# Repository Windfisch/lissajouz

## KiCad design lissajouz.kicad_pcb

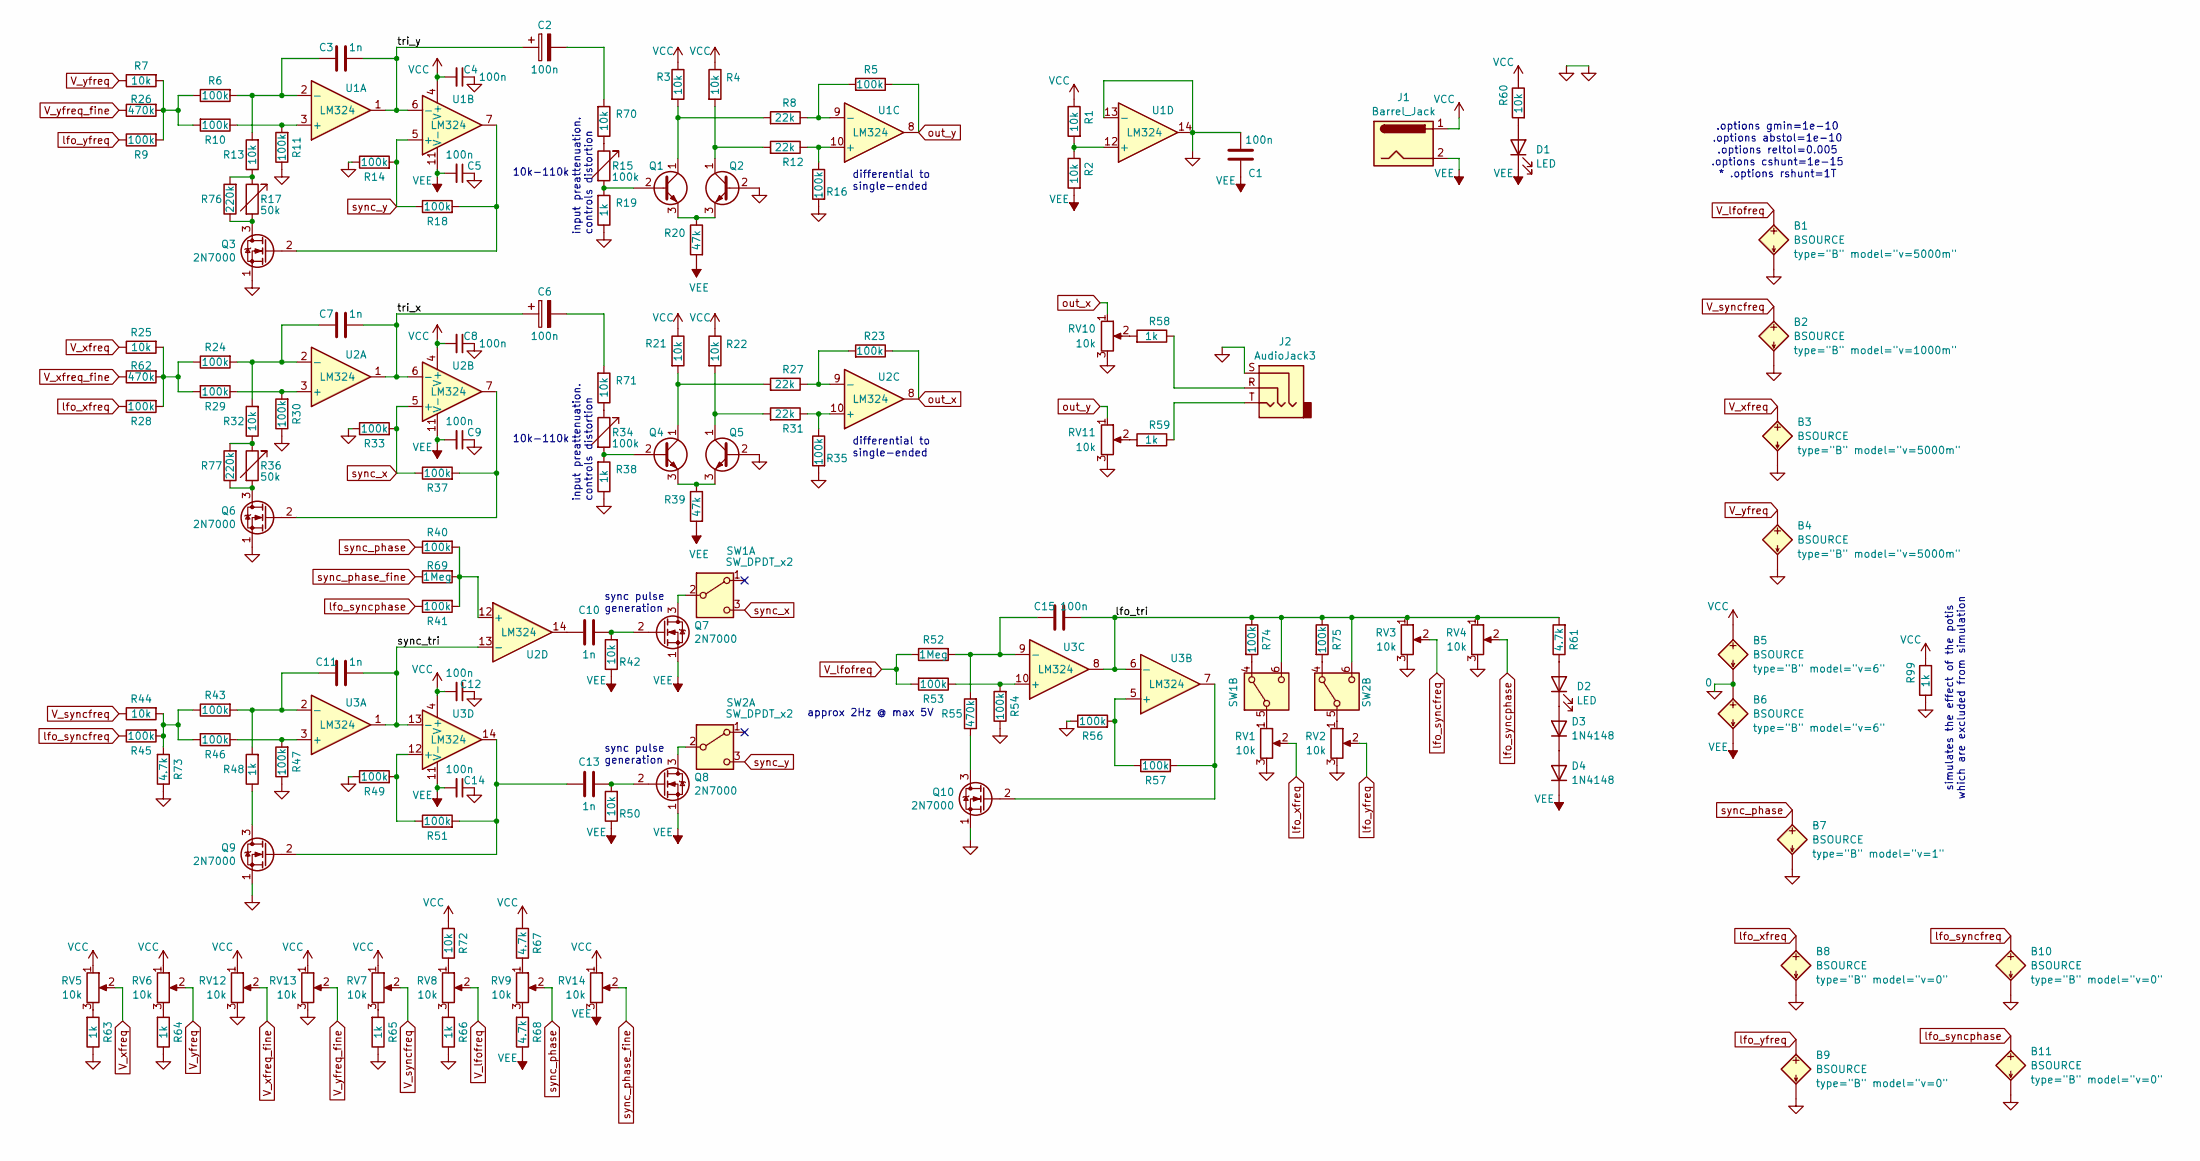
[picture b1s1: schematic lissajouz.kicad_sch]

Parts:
B1, B2, B3, B4, B5, B6, B7, B8, B9, B10, B11: BSOURCE
C1, C2, C4, C5, C6, C8, C9, C12, C14, C15: 100n; C_0805_2012Metric_Pad1.18x1.45mm_HandSolder
C3, C7, C10, C11, C13: 1n; C_0805_2012Metric_Pad1.18x1.45mm_HandSolder
D1, D2: LED; LED_D3.0mm
D3, D4: 1N4148; D_DO-35_SOD27_P7.62mm_Horizontal
J1: Barrel_Jack; myBarrelJack
J2: AudioJack3; Jack_3.5mm_CUI_SJ1-3535NG_Horizontal
Q1, Q2, Q4, Q5: BC547; TO-92_Inline
Q3, Q6, Q7, Q8, Q9, Q10: 2N7000; TO-92_Inline
R1, R2, R3, R4, R7, R13, R21, R22, R25, R32, R42, R44, R50, R60, R70, R71, R72: 10k; R_0805_2012Metric_Pad1.20x1.40mm_HandSolder
R5, R6, R9, R10, R11, R14, R16, R18, R23, R24, R28, R29, R30, R33, R35, R37, R40, R41, R43, R45, R46, R47, R49, R51, R53, R54, R56, R57, R74, R75: 100k; R_0805_2012Metric_Pad1.20x1.40mm_HandSolder
R8, R12, R27, R31: 22k; R_0805_2012Metric_Pad1.20x1.40mm_HandSolder
R15, R34: 100k; my_poti_Potentiometer_Alpha_RD901F-40-00D_Single_Vertical
R17, R36: 50k; my_poti_Potentiometer_Alpha_RD901F-40-00D_Single_Vertical
R19, R38, R48, R58, R59, R63, R64, R65, R66: 1k; R_0805_2012Metric_Pad1.20x1.40mm_HandSolder
R20, R39: 47k; R_0805_2012Metric_Pad1.20x1.40mm_HandSolder
R26, R55, R62: 470k; R_0805_2012Metric_Pad1.20x1.40mm_HandSolder
R52, R69: 1Meg; R_0805_2012Metric_Pad1.20x1.40mm_HandSolder
R61, R67, R68, R73: 4.7k; R_0805_2012Metric_Pad1.20x1.40mm_HandSolder
R76, R77: 220k; R_0805_2012Metric_Pad1.20x1.40mm_HandSolder
R99: 1k; R_0805_2012Metric_Pad1.15x1.40mm_HandSolder
RV1, RV2, RV3, RV4, RV5, RV6, RV7, RV8, RV9, RV12, RV13, RV14: 10k; my_poti_Potentiometer_Alpha_RD901F-40-00D_Single_Vertical
RV10, RV11: 10k; Potentiometer_Runtron_RM-065_Vertical
SW1, SW2: SW_DPDT_x2; switch8x8
U1, U2, U3: LM324; DIP-14_W7.62mm

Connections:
/lfo_tri: C15.1, R61.2, R74.1, R75.1, RV3.1, RV4.1, SW1.6 (C), SW2.6 (C), U3.6 (-), U3.8
/sync_tri: C11.1, U2.13 (-), U3.1, U3.13 (-)
/tri_x: C6.1, C7.1, U2.1, U2.6 (-)
/tri_y: C2.1, C3.1, U1.1, U1.6 (-)
GND: B1.2 (N-), B2.2 (N-), B3.2 (N-), B4.2 (N-), B7.2 (N-), B8.2 (N-), B9.2 (N-), B10.2 (N-), B11.2 (N-), C1.1, C4.1, C5.1, C8.1, C9.1, C12.1, C14.1, J2.S, Q2.2 (B), Q3.1 (S), Q5.2 (B), Q6.1 (S), Q9.1 (S), Q10.1 (S), R11.1, R14.1, R16.2, R19.1, R30.1, R33.1, R35.2, R38.1, R47.1, R49.1, R54.1, R56.1, R63.1, R64.1, R65.1, R66.1, R73.1, R99.2, RV1.3, RV2.3, RV3.3, RV4.3, RV10.3, RV11.3, RV12.3, RV13.3, U1.13 (-), U1.14
unnamed: B5.2 (N-), B6.1 (N+)
unnamed: C2.2, R70.2
unnamed: C6.2, R71.2
unnamed: C10.2, U2.14
unnamed: D1.2 (A), R60.2
unnamed: D2.2 (A), R61.1
unnamed: D2.1 (K), D3.2 (A)
unnamed: D3.1 (K), D4.2 (A)
unnamed: J2.R, R58.1
unnamed: J2.T, R59.1
unnamed: Q1.2 (B), R15.2, R19.2
unnamed: Q1.1 (C), R3.2, R8.2
unnamed: Q1.3 (E), Q2.3 (E), R20.1
unnamed: Q2.1 (C), R4.2, R12.2
unnamed: Q3.3 (D), R17.2, R76.1
unnamed: Q3.2 (G), R18.2, U1.7
unnamed: Q4.2 (B), R34.2, R38.2
unnamed: Q4.1 (C), R21.2, R27.2
unnamed: Q4.3 (E), Q5.3 (E), R39.1
unnamed: Q5.1 (C), R22.2, R31.2
unnamed: Q6.3 (D), R36.2, R77.1
unnamed: Q6.2 (G), R37.2, U2.7
unnamed: Q7.3 (D), SW1.2 (B)
unnamed: C10.1, Q7.2 (G), R42.2
unnamed: Q8.3 (D), SW2.2 (B)
unnamed: C13.1, Q8.2 (G), R50.2
unnamed: Q9.3 (D), R48.1
unnamed: C13.2, Q9.2 (G), R51.2, U3.14
unnamed: Q10.3 (D), R55.1
unnamed: Q10.2 (G), R57.2, U3.7
unnamed: R6.1, R7.2, R9.2, R10.2, R26.2
unnamed: R13.1, R17.1, R76.2
unnamed: R15.1, R70.1
unnamed: R24.1, R25.2, R28.2, R29.2, R62.2
unnamed: R32.1, R36.1, R77.2
unnamed: R34.1, R71.1
unnamed: R43.1, R44.2, R45.2, R46.2, R73.2
unnamed: R58.2, RV10.2
unnamed: R59.2, RV11.2
unnamed: R63.2, RV5.3
unnamed: R64.2, RV6.3
unnamed: R65.2, RV7.3
unnamed: R66.2, RV8.3
unnamed: R67.1, RV9.1
unnamed: R68.2, RV9.3
unnamed: R72.1, RV8.1
unnamed: R74.2, SW1.4 (A)
unnamed: RV1.1, SW1.5 (B)
unnamed: R75.2, SW2.4 (A)
unnamed: RV2.1, SW2.5 (B)
unnamed: R10.1, R11.2, U1.3 (+)
unnamed: C3.2, R6.2, R13.2, U1.2 (-)
unnamed: R12.1, R16.1, U1.10 (+)
unnamed: R5.2, R8.1, U1.9 (-)
unnamed: R1.2, R2.1, U1.12 (+)
unnamed: R29.1, R30.2, U2.3 (+)
unnamed: C7.2, R24.2, R32.2, U2.2 (-)
unnamed: R31.1, R35.1, U2.10 (+)
unnamed: R23.2, R27.1, U2.9 (-)
unnamed: R40.2, R41.2, R69.2, U2.12 (+)
unnamed: R46.1, R47.2, U3.3 (+)
unnamed: C11.2, R43.2, R48.2, U3.2 (-)
unnamed: R56.2, R57.1, U3.5 (+)
unnamed: R53.1, R54.2, U3.10 (+)
unnamed: C15.2, R52.2, R55.2, U3.9 (-)
unnamed: R49.2, R51.1, U3.12 (+)
VCC: B5.1 (N+), C4.2, C8.2, C12.2, J1.1, R1.1, R3.1, R4.1, R21.1, R22.1, R60.1, R67.2, R72.2, R99.1, RV5.1, RV6.1, RV7.1, RV12.1, RV13.1, RV14.1, U1.4 (V+), U2.4 (V+), U3.4 (V+)
VEE: B6.2 (N-), C1.2, C5.2, C9.2, C14.2, D1.1 (K), D4.1 (K), J1.2, Q7.1 (S), Q8.1 (S), R2.2, R20.2, R39.2, R42.1, R50.1, R68.1, RV14.3, U1.11 (V-), U2.11 (V-), U3.11 (V-)
V_lfofreq: B1.1 (N+), R52.1, R53.2, RV8.2
V_syncfreq: B2.1 (N+), R44.1, RV7.2
V_xfreq: B3.1 (N+), R25.1, RV5.2
V_xfreq_fine: R62.1, RV12.2
V_yfreq: B4.1 (N+), R7.1, RV6.2
V_yfreq_fine: R26.1, RV13.2
lfo_syncfreq: B10.1 (N+), R45.1, RV3.2
lfo_syncphase: B11.1 (N+), R41.1, RV4.2
lfo_xfreq: B8.1 (N+), R28.1, RV1.2
lfo_yfreq: B9.1 (N+), R9.1, RV2.2
out_x: R23.1, RV10.1, U2.8
out_y: R5.1, RV11.1, U1.8
sync_phase: B7.1 (N+), R40.1, RV9.2
sync_phase_fine: R69.1, RV14.2
sync_x: R33.2, R37.1, SW1.3 (C), U2.5 (+)
sync_y: R14.2, R18.1, SW2.3 (C), U1.5 (+)

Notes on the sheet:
differential to single-ended
sync pulse generation
simulates the effect of the potis which are excluded from simulation
approx 2Hz @ max 5V
10k-110k
input preattenuation. controls distortion
.options gmin=1e-10 .options abstol=1e-10 .options reltol=0.005 .options cshunt=1e-15 * .options rshunt=1T

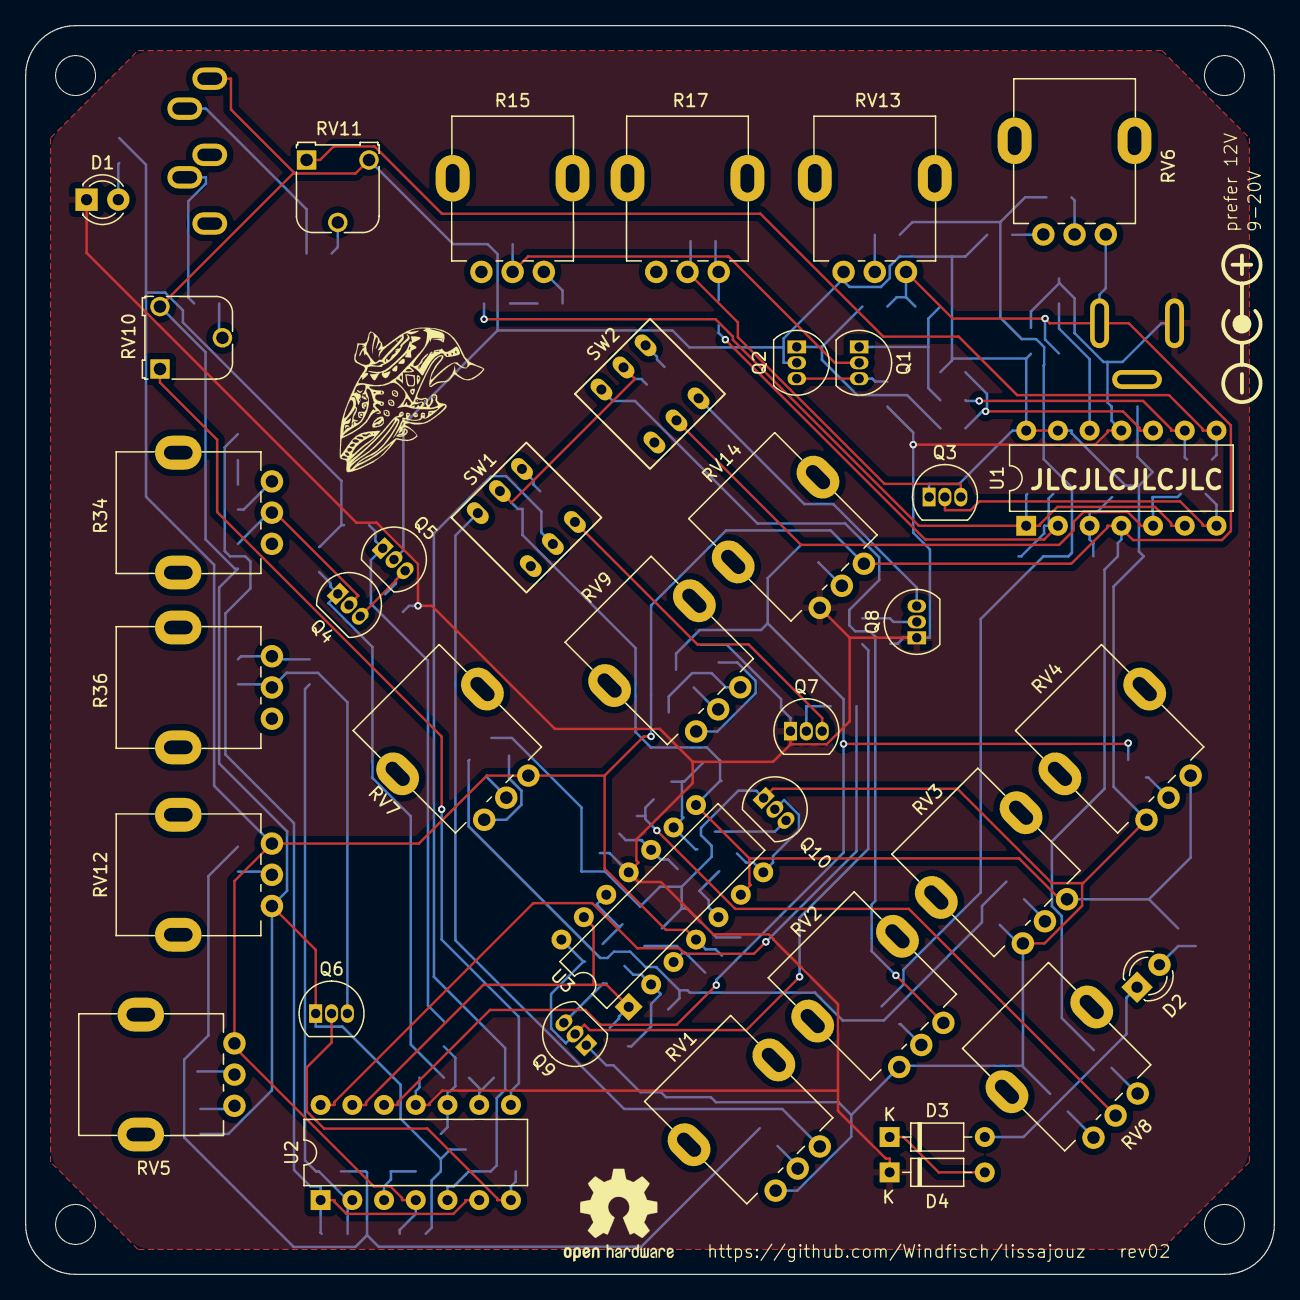
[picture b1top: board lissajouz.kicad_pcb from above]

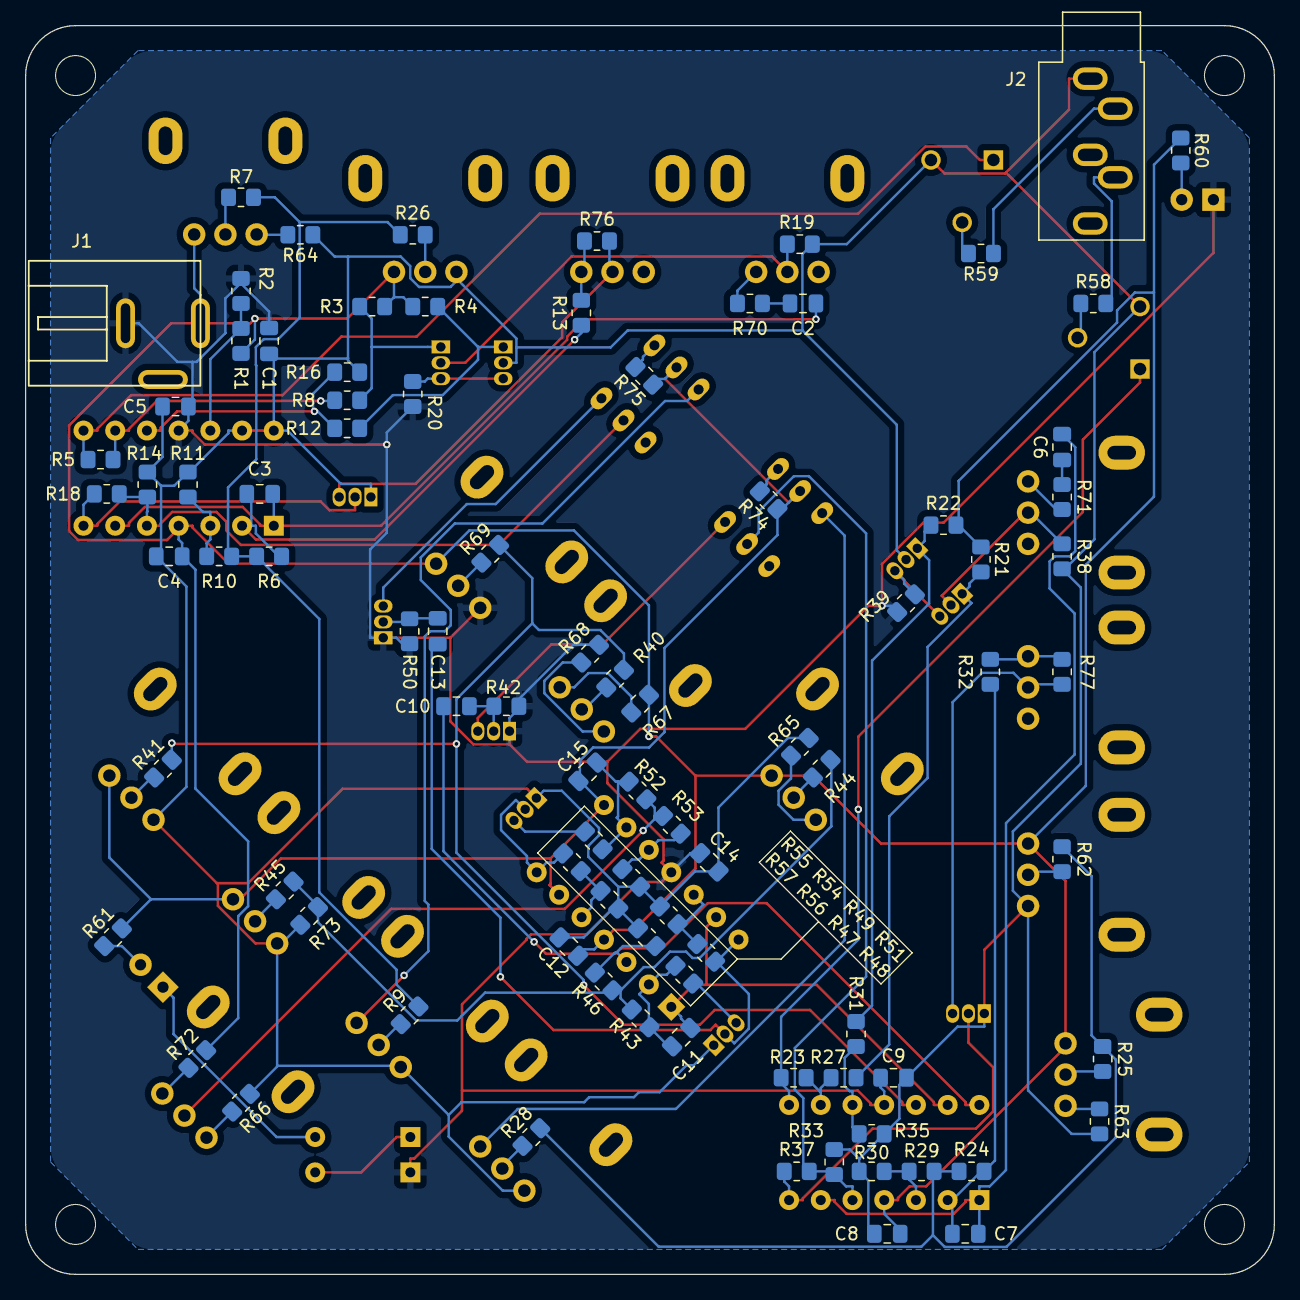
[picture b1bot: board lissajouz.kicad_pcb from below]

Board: 2 copper layers, 100.0 x 100.0 mm, 132 parts (90 on the bottom side), 88 nets.

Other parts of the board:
HOLE1, HOLE2, HOLE3, HOLE4: MountingHole_3.2mm_M3
wf: LOGO; windfisch_smaller

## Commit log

2024-08-07 initial
2024-08-07 tried simulation, does not work
2024-08-08 it wörx
2024-08-08 tuning
2024-08-08 closer to the real thing
2024-08-08 more betterer
2024-08-08 close to final
2024-08-08 reannotate schematic
2024-08-08 add most footprints
2024-08-11 kinda final-ish UI layout
2024-08-11 all components positioned
2024-08-11 minimal routing
2024-08-12 board adjustments
2024-08-13 frontplate first attempt
2024-08-13 frontplate++
2024-08-13 more frontplate
2024-08-13 frontplate almost done
2024-08-13 frontplate finished
2024-08-13 make gingerbread happy
2024-08-13 frontplate PCB
2024-08-13 add font used
2024-08-13 missing file
2024-09-04 Schematic fixes, did not update PCB yet!
    - Darken LEDs by increasing resistors R60 and R61 to 10k each
    - LFO LED: go closer to "dark" by adding second diode D4
    - Move LFO frequency range down (decrease low-end R66 and add new top-end R72)
    - Decrease minimum and maximum syncfreq range (4.7k R73 to GND)
    - Increase "freq fine" resistors R26 and R62 to 470k
    - Fix wrong BJT transistor values
2024-09-07 Fine-tuning and fix switch footprint
    - fine-tune slant poti range
    - reduce x/y freq lfo when not synced
2024-09-07 Fix bugs in PCB
2024-09-09 Final adjustments for rev02
